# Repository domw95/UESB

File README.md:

# UESB
## Ultimate ESC Switcher Board.

A device to control up to 6 brushed DC motors from 2 radio control input signals. The firmware is configued to drive 1 motor at a time via 1 input signal, and switch between based on the other.

[More details](https://domwil.co.uk/posts/uesb/)

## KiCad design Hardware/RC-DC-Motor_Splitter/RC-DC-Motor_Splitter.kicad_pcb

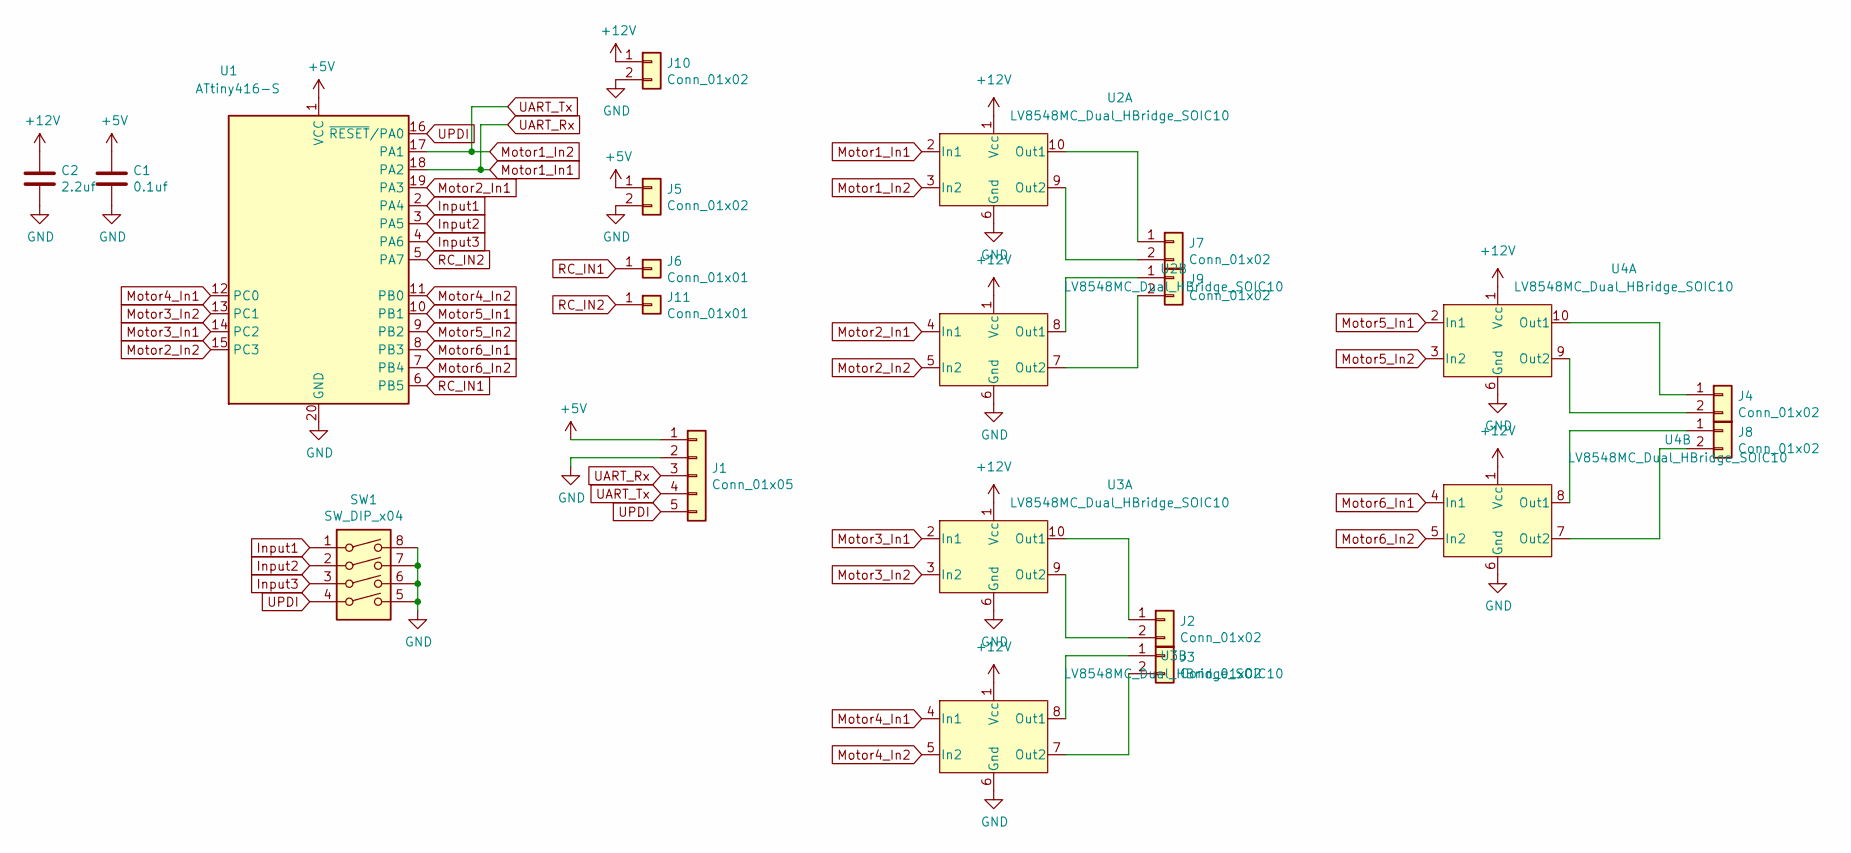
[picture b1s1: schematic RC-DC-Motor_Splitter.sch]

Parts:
C1: 0.1uf; C_1206_3216Metric_Pad1.33x1.80mm_HandSolder
C2: 2.2uf; C_1206_3216Metric_Pad1.33x1.80mm_HandSolder
J1: Conn_01x05; PinHeader_1x05_P2.54mm_Vertical
J2, J3, J4, J5, J7, J8, J9, J10: Conn_01x02; Motor_Pad
J6, J11: Conn_01x01; Single_Pad
SW1: SW_DIP_x04; SOIC-8-Extended_pads_dip-switch; LCSC C132838
U1: ATtiny416-S; SOIC-20W_7.5x12.8mm_P1.27mm; LCSC C145622
U2, U3, U4: LV8548MC_Dual_HBridge_SOIC10; SOIC-10_3.9x4.9mm_P1.00mm; LCSC C19950

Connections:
+5V: C1.1, J1.1, J5.1, U1.1 (VCC)
+12V: C2.1, J10.1, U2.1 (Vcc), U3.1 (Vcc), U4.1 (Vcc)
GND: C1.2, C2.2, J1.2, J5.2, J10.2, SW1.5, SW1.6, SW1.7, SW1.8, U1.20 (GND), U2.6 (Gnd), U3.6 (Gnd), U4.6 (Gnd)
Input1: SW1.1, U1.2 (PA4)
Input2: SW1.2, U1.3 (PA5)
Input3: SW1.3, U1.4 (PA6)
Motor1_In1: J1.3, U1.18 (PA2), U2.2 (In1)
Motor1_In2: J1.4, U1.17 (PA1), U2.3 (In2)
Motor2_In1: U1.19 (PA3), U2.4 (In1)
Motor2_In2: U1.15 (PC3), U2.5 (In2)
Motor3_In1: U1.14 (PC2), U3.2 (In1)
Motor3_In2: U1.13 (PC1), U3.3 (In2)
Motor4_In1: U1.12 (PC0), U3.4 (In1)
Motor4_In2: U1.11 (PB0), U3.5 (In2)
Motor5_In1: U1.10 (PB1), U4.2 (In1)
Motor5_In2: U1.9 (PB2), U4.3 (In2)
Motor6_In1: U1.8 (PB3), U4.4 (In1)
Motor6_In2: U1.7 (PB4), U4.5 (In2)
unnamed: J2.1, U3.10 (Out1)
unnamed: J2.2, U3.9 (Out2)
unnamed: J3.1, U3.8 (Out1)
unnamed: J3.2, U3.7 (Out2)
unnamed: J4.1, U4.10 (Out1)
unnamed: J4.2, U4.9 (Out2)
unnamed: J7.1, U2.10 (Out1)
unnamed: J7.2, U2.9 (Out2)
unnamed: J8.1, U4.8 (Out1)
unnamed: J8.2, U4.7 (Out2)
unnamed: J9.1, U2.8 (Out1)
unnamed: J9.2, U2.7 (Out2)
RC_IN1: J6.1, U1.6 (PB5)
RC_IN2: J11.1, U1.5 (PA7)
UPDI: J1.5, SW1.4, U1.16 (~RESET~/PA0)

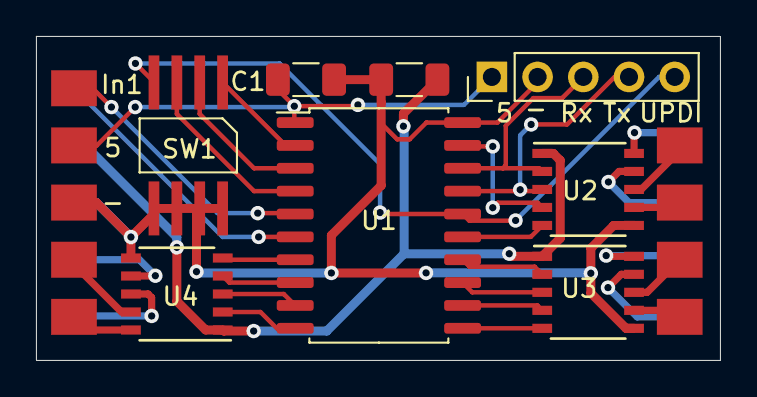
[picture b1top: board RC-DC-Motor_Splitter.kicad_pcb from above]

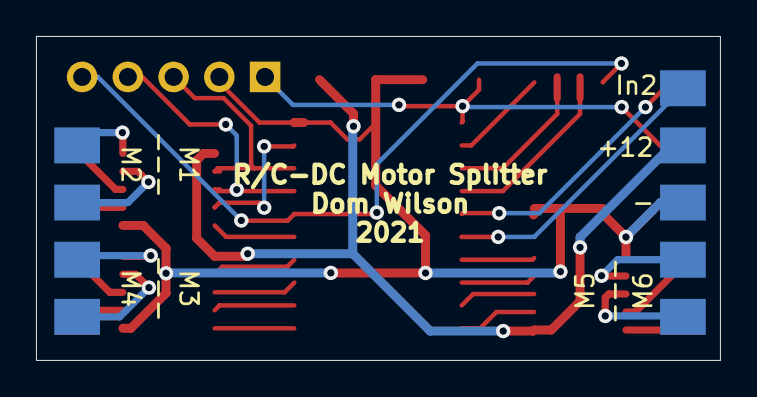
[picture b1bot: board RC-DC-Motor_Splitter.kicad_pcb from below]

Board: 2 copper layers, 38.0 x 18.0 mm, 18 parts (5 on the bottom side), 33 nets.

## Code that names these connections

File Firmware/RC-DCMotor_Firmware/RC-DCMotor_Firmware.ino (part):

// Motor Pins
// Motor   | Portpin | GPIO  | Pin
// Motor 1 | PA2 PA1 | 15 14 | 18 17
// Motor 2 | PA3 PC3 | 16 13 | 19 15
// Motor 3 | PC2 PC1 | 12 11 | 14 13
// Motor 4 | PC0 PB0 | 10 9  | 12 11
// Motor 5 | PB1 PB2 | 8 7   | 10 9
// Motor 6 | PB3 PB4 | 6 5   | 8 7

// Input Pins
// SWITCH | Pin
// 1      | UPDI
// 2      | PA6
// 3      | PA5
// 4      | PA4

// RC Pins
// PB5
// PA7

// #define SERIALDEBUG

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
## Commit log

2021-01-23 Created KiCad Project
2021-01-23 New Small Design
2021-01-23 Added pdf schematic
2021-01-25 Production Design
2021-02-15 Firmware + some hardware test programs
2021-03-18 Reorganise
2021-03-18 Added Docs and datasheets
2021-03-18 Docs update
